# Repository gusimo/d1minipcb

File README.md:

### Simple PCB for Wemos D1 mini projects

- pre wired for default sensors
- mini breadboard
- can use resistors or bridge them
- options to pull your own lines to the breadboard or for debugging
- 7x7cm to fit into standard plastic boxes

My first PCB Design, it has some flaws, will remove the rectangular corners soon and rewire few pinouts.

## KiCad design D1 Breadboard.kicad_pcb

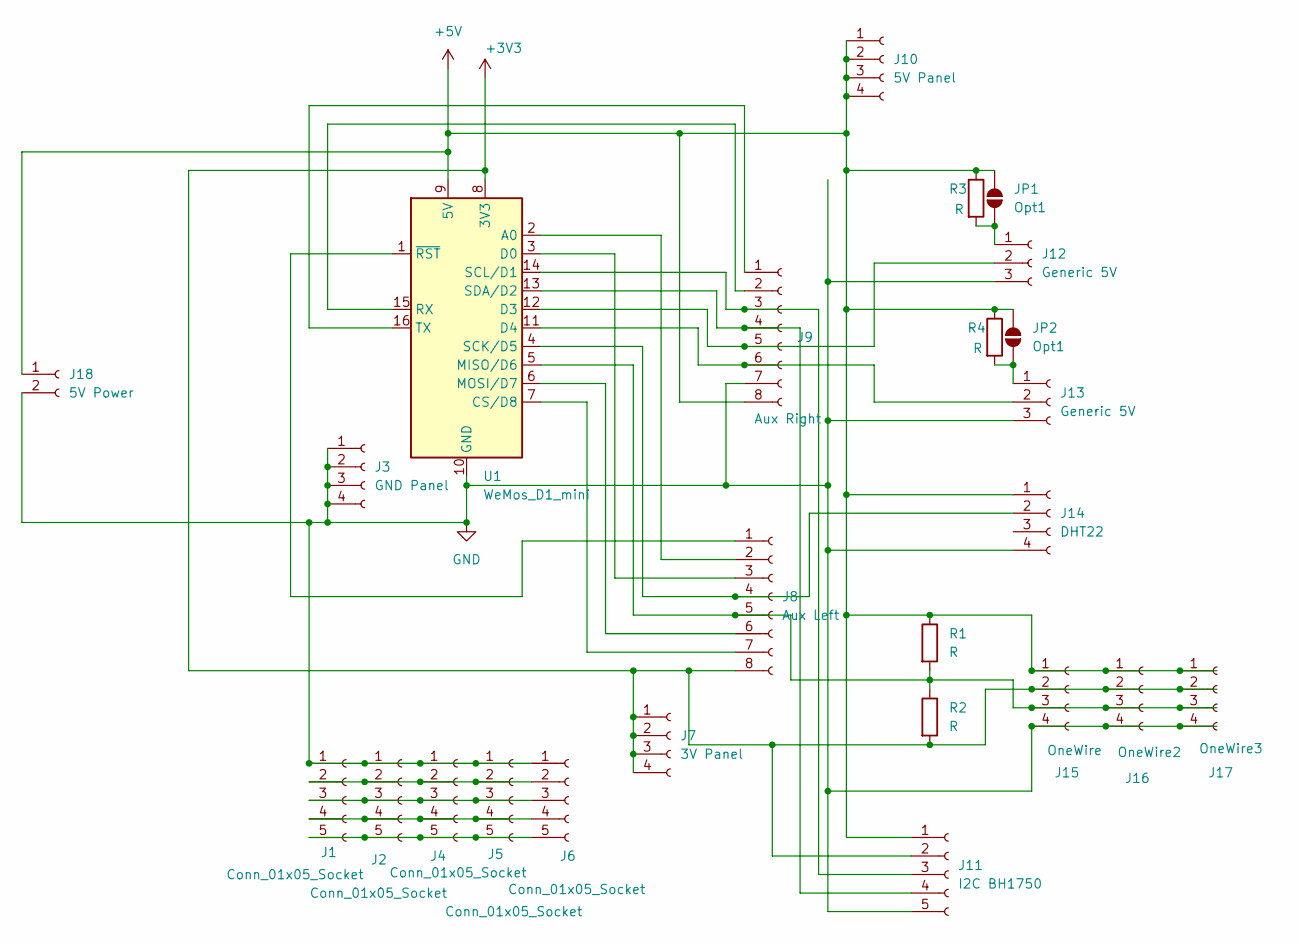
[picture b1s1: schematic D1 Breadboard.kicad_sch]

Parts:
J1, J2, J4, J5, J6: Conn_01x05_Socket; PinHeader_1x05_P2.54mm_Vertical
J3: GND Panel; PinHeader_1x04_P2.54mm_Vertical
J7: 3V Panel; PinHeader_1x04_P2.54mm_Vertical
J8: Aux Left; PinHeader_1x08_P2.54mm_Vertical
J9: Aux Right; PinHeader_1x08_P2.54mm_Vertical
J10: 5V Panel; PinHeader_1x04_P2.54mm_Vertical
J11: I2C BH1750; PinHeader_1x05_P2.54mm_Vertical
J12, J13: Generic 5V; JST_XH_B3B-XH-A_1x03_P2.50mm_Vertical
J14: DHT22; PinHeader_1x04_P2.54mm_Vertical
J15: OneWire; PinHeader_1x04_P2.54mm_Vertical
J16: OneWire2; PinHeader_1x04_P2.54mm_Vertical
J17: OneWire3; PinHeader_1x04_P2.54mm_Vertical
J18: 5V Power; JST_XH_B2B-XH-AM_1x02_P2.50mm_Vertical
JP1, JP2: Opt1; SolderJumper-2_P1.3mm_Open_RoundedPad1.0x1.5mm
R1, R2: R; R_Axial_DIN0204_L3.6mm_D1.6mm_P7.62mm_Horizontal
R3, R4: R; R_Axial_DIN0204_L3.6mm_D1.6mm_P5.08mm_Vertical
U1: WeMos_D1_mini; WEMOS_D1_mini_light

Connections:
+3V3: J7.1, J7.2, J7.3, J7.4, J8.8, J11.2, J15.2, J16.2, J17.2, R2.2, U1.8 (3V3)
+5V: J9.8, J10.1, J10.2, J10.3, J10.4, J11.1, J14.1, J15.1, J16.1, J17.1, J18.1, JP1.1 (A), JP2.1 (A), R1.1, R3.1, R4.1, U1.9 (5V)
GND: J1.1, J2.1, J3.1, J3.2, J3.3, J3.4, J4.1, J5.1, J6.1, J9.7, J11.5, J12.3, J13.3, J14.4, J15.4, J16.4, J17.4, J18.2, U1.10 (GND)
unnamed: J1.2, J2.2, J4.2, J5.2, J6.2
unnamed: J1.3, J2.3, J4.3, J5.3, J6.3
unnamed: J1.4, J2.4, J4.4, J5.4, J6.4
unnamed: J1.5, J2.5, J4.5, J5.5, J6.5
unnamed: J8.1, U1.1 (~RST)
unnamed: J8.2, U1.2 (A0)
unnamed: J8.3, U1.3 (D0)
unnamed: J8.6, U1.6 (MOSI/D7)
unnamed: J8.7, U1.7 (CS/D8)
unnamed: J9.1, U1.16 (TX)
unnamed: J9.2, U1.15 (RX)
unnamed: J9.3, J11.3, U1.14 (SCL/D1)
unnamed: J9.4, J11.4, U1.13 (SDA/D2)
unnamed: J12.1, JP1.2 (B), R3.2
unnamed: J9.5, J12.2, U1.12 (D3)
unnamed: J13.1, JP2.2 (B), R4.2
unnamed: J9.6, J13.2, U1.11 (D4)
unnamed: J8.4, J14.2, U1.4 (SCK/D5)
unnamed: J8.5, J15.3, J16.3, J17.3, R1.2, R2.1, U1.5 (MISO/D6)

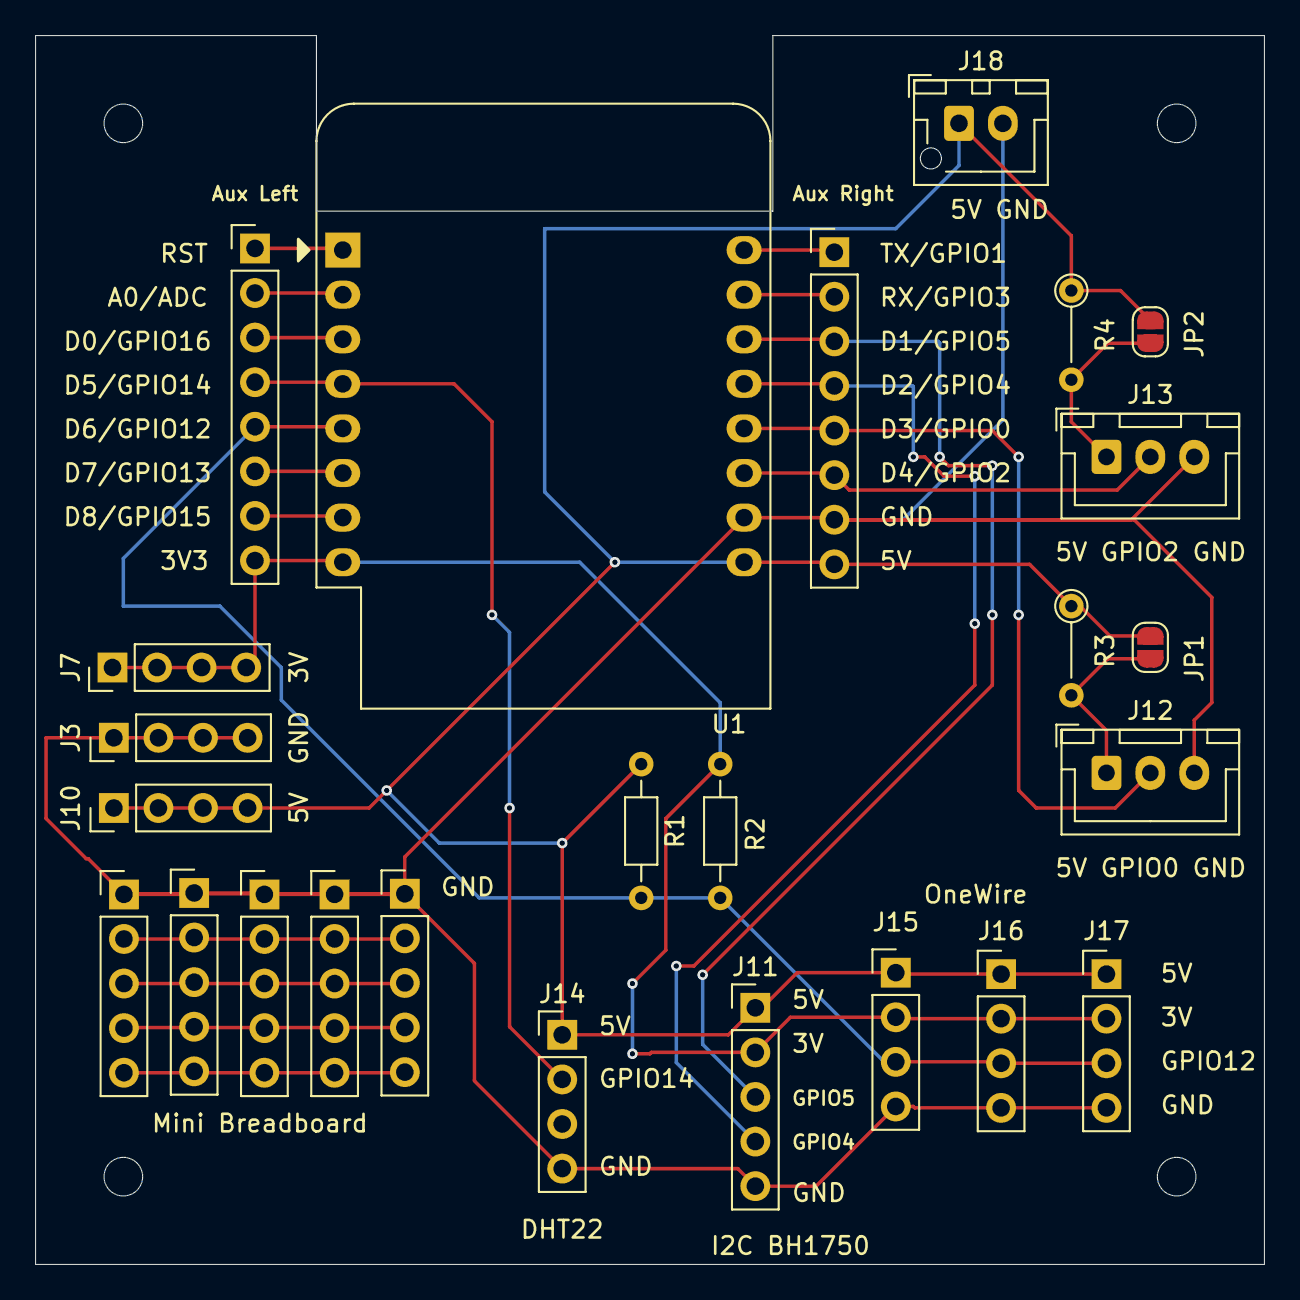
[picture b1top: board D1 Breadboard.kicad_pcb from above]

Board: 2 copper layers, 70.0 x 70.0 mm, 25 parts (0 on the bottom side), 22 nets.
